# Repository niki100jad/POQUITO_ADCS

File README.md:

# POQUITO_ADCS

An ADCS PCB for a PocketQube, designed for the [QUBIK platform](https://libre.space/projects/qubik/).

This project is based on the https://gitlab.com/librespacefoundation/pq9ish/pq9ish-comms-vu-hw
project by the Libre Space Foundation, which was used for the [QUBIK](https://libre.space/projects/qubik/)
PocketQube missions.

## Features

- 3 magnetorquer drivers
- 1 9-axis Inertial Measurement Unit
- Based on an STM32L476 MCU
- Compatible with the [PQ9 standard](https://dataverse.nl/dataset.xhtml?persistentId=doi:10.34894/6MVBCZ)

## Images

## Related Projects

- [POQUITO Panels](https://github.com/kongr45gpen/POQUITO-panels)

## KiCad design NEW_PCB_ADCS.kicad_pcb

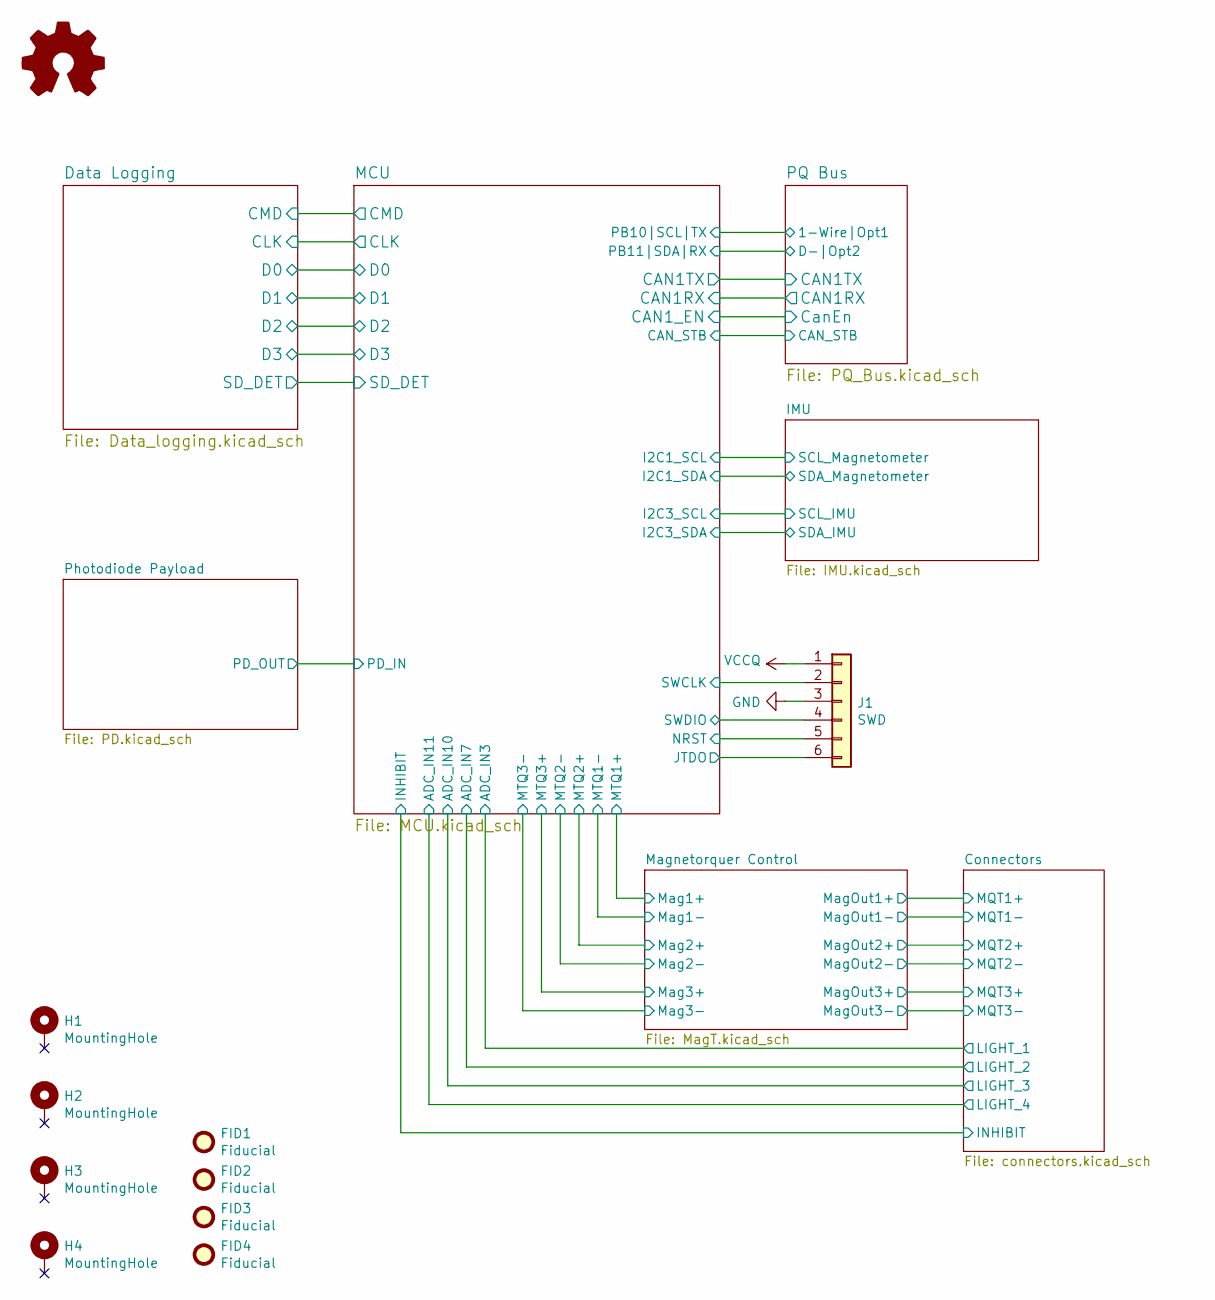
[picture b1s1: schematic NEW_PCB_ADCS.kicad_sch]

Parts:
FID1, FID2, FID3, FID4: Fiducial; Fiducial_0.5mm_Mask1.5mm
H1, H2, H3, H4: MountingHole; MountingHole_2.5mm_Pad
J1: SWD; Molex_PicoBlade_53261-0671_1x06-1MP_P1.25mm_Horizontal; Part Number 53261-0671

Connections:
/MCU/JTDO: J1.6; also elsewhere on the board
/MCU/NRST: J1.5; also elsewhere on the board
/MCU/SWCLK: J1.2; also elsewhere on the board
/MCU/SWDIO: J1.4; also elsewhere on the board
GND: J1.3; also elsewhere on the board
VCCQ: J1.1; also elsewhere on the board

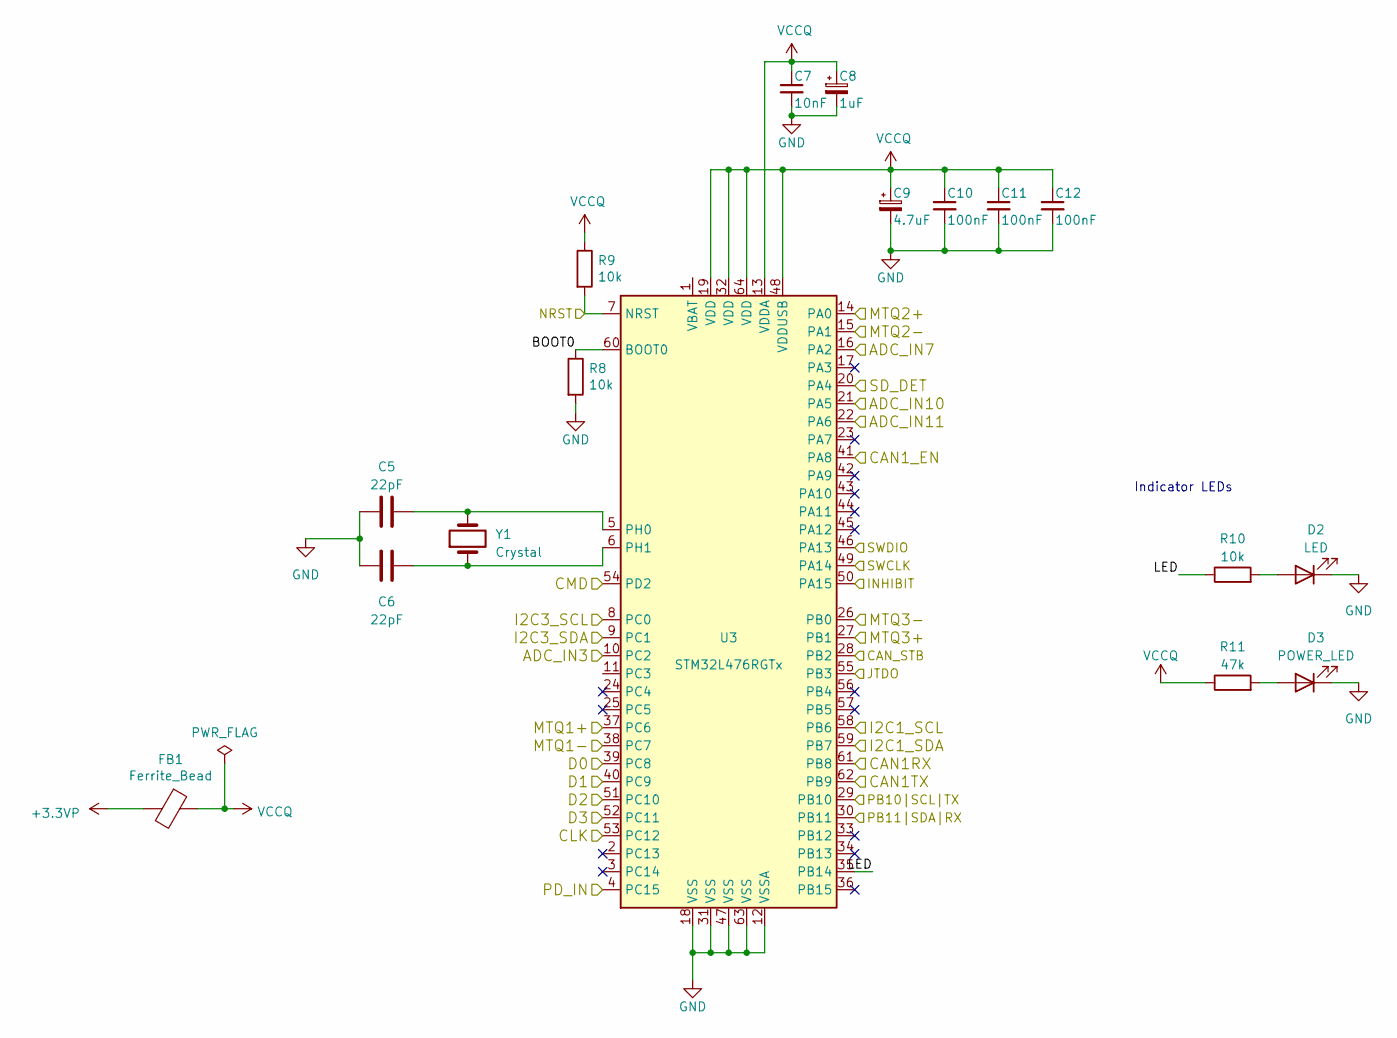
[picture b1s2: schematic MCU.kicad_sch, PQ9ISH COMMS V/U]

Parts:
C5, C6: 22pF; C_0603_1608Metric
C7: 10nF; C_0603_1608Metric_Pad1.08x0.95mm_HandSolder; Part Number C0603C103K9RACTU
C8: 1uF; C_0603_1608Metric_Pad1.08x0.95mm_HandSolder; Part Number CGB3B3X6S1A105K055AB
C9: 4.7uF; C_0603_1608Metric_Pad1.08x0.95mm_HandSolder; Part Number GRT188R60J475KE01D
C10, C11, C12: 100nF; C_0603_1608Metric; Part Number C0603C104K9RACTU
D2: LED; LED_0603_1608Metric; MPN LTST-C190KFKT
D3: POWER_LED; LED_0603_1608Metric; MPN LTST-C190KRKT
FB1: Ferrite_Bead; L_0603_1608Metric_Pad1.05x0.95mm_HandSolder; Part Number 742792664
R8, R9: 10k; R_0603_1608Metric; Part Number RE0603BRE0710KL
R10: 10k; R_0603_1608Metric; MPN RE0603BRE0710KL
R11: 47k; R_0603_1608Metric; Part Number RMCF0603FT47K0
U3: STM32L476RGTx; LQFP-64_10x10mm_P0.5mm; Part Number STM32L476RGT6
Y1: Crystal; Crystal_SMD_ECS_CSM3X-2Pin_7.6x4.1mm; MPN ECS-80-18-5PX-CKM-TR

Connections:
+3.3VP: FB1.2; also elsewhere on the board
/Connectors/INHIBIT: U3.50 (PA15); also elsewhere on the board
/Connectors/LIGHT_1: U3.10 (PC2); also elsewhere on the board
/Connectors/LIGHT_2: U3.16 (PA2); also elsewhere on the board
/Connectors/LIGHT_3: U3.21 (PA5); also elsewhere on the board
/Connectors/LIGHT_4: U3.22 (PA6); also elsewhere on the board
/Data Logging/CLK: U3.53 (PC12); also elsewhere on the board
/Data Logging/CMD: U3.54 (PD2); also elsewhere on the board
/Data Logging/D0: U3.39 (PC8); also elsewhere on the board
/Data Logging/D1: U3.40 (PC9); also elsewhere on the board
/Data Logging/D2: U3.51 (PC10); also elsewhere on the board
/Data Logging/D3: U3.52 (PC11); also elsewhere on the board
/Data Logging/SD_DET: U3.20 (PA4); also elsewhere on the board
/IMU/SCL_IMU: U3.8 (PC0); also elsewhere on the board
/IMU/SCL_Magnetometer: U3.58 (PB6); also elsewhere on the board
/IMU/SDA_IMU: U3.9 (PC1); also elsewhere on the board
/IMU/SDA_Magnetometer: U3.59 (PB7); also elsewhere on the board
/MCU/BOOT0: R8.1, U3.60 (BOOT0)
/MCU/CAN1RX: U3.61 (PB8); also elsewhere on the board
/MCU/CAN1TX: U3.62 (PB9); also elsewhere on the board
/MCU/CAN1_EN: U3.41 (PA8); also elsewhere on the board
/MCU/CAN_STB: U3.28 (PB2); also elsewhere on the board
/MCU/JTDO: U3.55 (PB3); also elsewhere on the board
/MCU/LED: R10.1, U3.35 (PB14)
/MCU/MTQ1+: U3.37 (PC6); also elsewhere on the board
/MCU/MTQ1-: U3.38 (PC7); also elsewhere on the board
/MCU/MTQ2+: U3.14 (PA0); also elsewhere on the board
/MCU/MTQ2-: U3.15 (PA1); also elsewhere on the board
/MCU/MTQ3+: U3.27 (PB1); also elsewhere on the board
/MCU/MTQ3-: U3.26 (PB0); also elsewhere on the board
/MCU/NRST: R9.2, U3.7 (NRST); also elsewhere on the board
/MCU/PB10|SCL|TX: U3.29 (PB10); also elsewhere on the board
/MCU/PB11|SDA|RX: U3.30 (PB11); also elsewhere on the board
/MCU/PD_IN: U3.4 (PC15); also elsewhere on the board
/MCU/SWCLK: U3.49 (PA14); also elsewhere on the board
/MCU/SWDIO: U3.46 (PA13); also elsewhere on the board
GND: C5.1, C6.1, C7.2, C8.2, C9.2, C10.2, C11.2, C12.2, D2.1 (K), D3.1 (K), R8.2, U3.12 (VSSA), U3.18 (VSS), U3.31 (VSS), U3.47 (VSS), U3.63 (VSS); also elsewhere on the board
unnamed: D2.2 (A), R10.2
unnamed: D3.2 (A), R11.2
unnamed: C5.2, U3.5 (PH0), Y1.2
unnamed: C6.2, U3.6 (PH1), Y1.1
VCCQ: C7.1, C8.1, C9.1, C10.1, C11.1, C12.1, FB1.1, R9.1, R11.1, U3.13 (VDDA), U3.19 (VDD), U3.32 (VDD), U3.48 (VDDUSB), U3.64 (VDD); also elsewhere on the board

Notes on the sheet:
Indicator LEDs

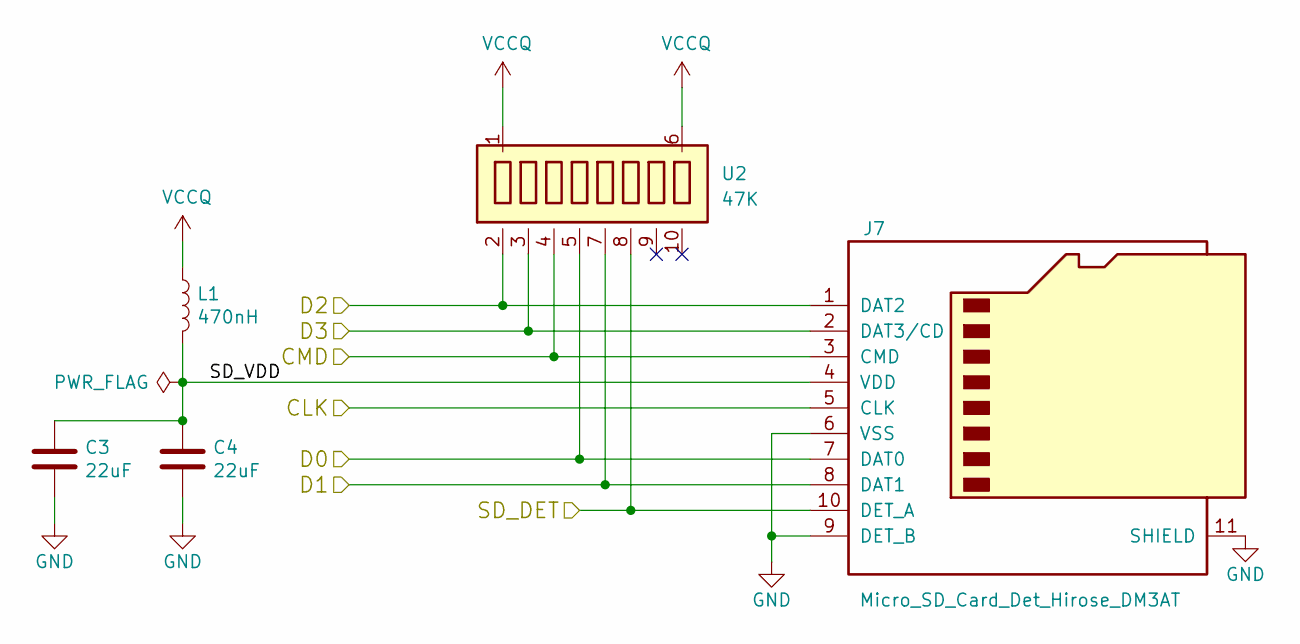
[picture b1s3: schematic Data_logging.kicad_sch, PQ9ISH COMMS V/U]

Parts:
C3, C4: 22uF; C_0603_1608Metric_Pad1.08x0.95mm_HandSolder; Part Number GRM188C80J226ME15D
J7: Micro_SD_Card_Det_Hirose_DM3AT; microSD_HC_Hirose_DM3D-SF; Part Number DM3D-SF
L1: 470nH; L_0603_1608Metric_Pad1.05x0.95mm_HandSolder; Part Number DFE18SANR47ME0L
U2: 47K; EXBD; Part Number EXBD10C473J

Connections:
/Data Logging/CLK: J7.5 (CLK); also elsewhere on the board
/Data Logging/CMD: J7.3 (CMD), U2.4 (R3); also elsewhere on the board
/Data Logging/D0: J7.7 (DAT0), U2.5 (R4); also elsewhere on the board
/Data Logging/D1: J7.8 (DAT1), U2.7 (R5); also elsewhere on the board
/Data Logging/D2: J7.1 (DAT2), U2.2 (R1); also elsewhere on the board
/Data Logging/D3: J7.2 (DAT3/CD), U2.3 (R2); also elsewhere on the board
/Data Logging/SD_DET: J7.10 (DET_A), U2.8 (R6); also elsewhere on the board
/Data Logging/SD_VDD: C3.1, C4.1, J7.4 (VDD), L1.2
GND: C3.2, C4.2, J7.6 (VSS), J7.9 (DET_B), J7.11 (SHIELD); also elsewhere on the board
VCCQ: L1.1, U2.1 (common), U2.6 (Common); also elsewhere on the board

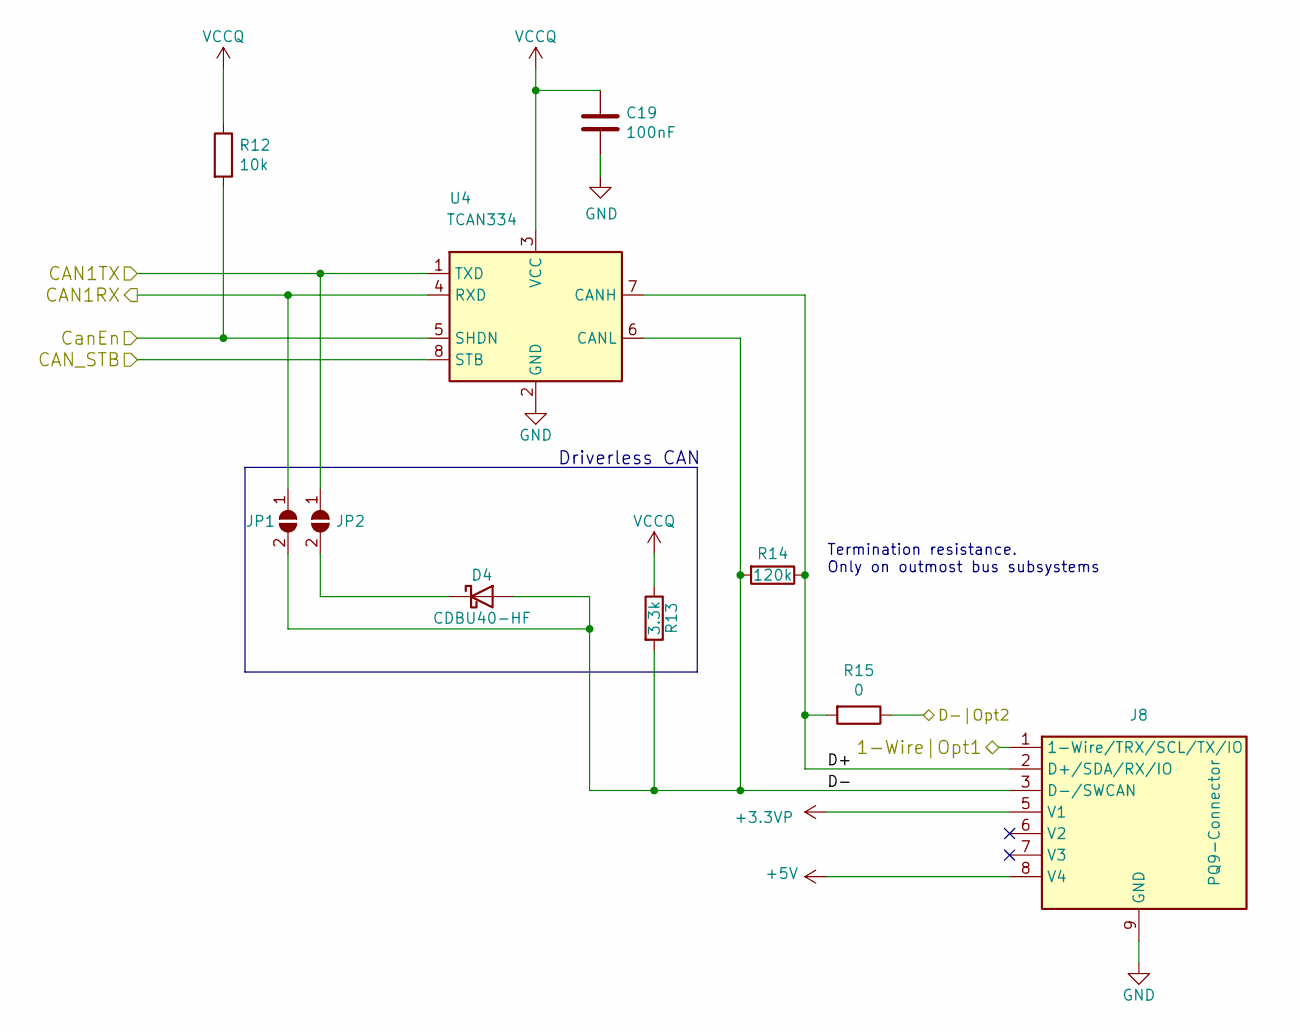
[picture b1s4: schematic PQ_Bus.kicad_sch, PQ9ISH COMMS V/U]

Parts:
C19: 100nF; C_0603_1608Metric; Part Number C0603C104K9RACTU
D4: CDBU40-HF; D_0603_1608Metric; Part Number CDBU40-HF
J8: PQ9-Connector; PinSocket_1x09_P2.00mm_Vertical; Part Number SQT-109-03-LS
JP1, JP2: SolderJumper_2_Open; SolderJumper-2_P1.3mm_Open_Pad1.0x1.5mm
R12: 10k; R_0603_1608Metric; Part Number RE0603BRE0710KL
R13: 3.3k; R_0603_1608Metric; Part Number MCT06030C3301FP500
R14: 120k; R_0603_1608Metric; Part Number CRCW0603120RFKEA
R15: 0; R_0603_1608Metric; Part Number RMCF0603ZT0R00
U4: TCAN334; SOT-23-8; Part Number TCAN334GDCNT

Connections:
+3.3VP: J8.5 (V1); also elsewhere on the board
+5V: J8.8 (V4)
/MCU/CAN1RX: JP1.1 (A), U4.4 (RXD); also elsewhere on the board
/MCU/CAN1TX: JP2.1 (A), U4.1 (TXD); also elsewhere on the board
/MCU/CAN1_EN: R12.2, U4.5 (SHDN); also elsewhere on the board
/MCU/CAN_STB: U4.8 (STB); also elsewhere on the board
/MCU/PB10|SCL|TX: J8.1 (1-Wire/TRX/SCL/TX/IO); also elsewhere on the board
/MCU/PB11|SDA|RX: R15.1; also elsewhere on the board
/PQ Bus/D+: J8.2 (D+/SDA/RX/IO), R14.1, R15.2, U4.7 (CANH)
/PQ Bus/D-: D4.2 (A), J8.3 (D-/SWCAN), JP1.2 (B), R13.2, R14.2, U4.6 (CANL)
GND: C19.2, J8.4 (GND), J8.9 (GND), U4.2 (GND); also elsewhere on the board
unnamed: D4.1 (K), JP2.2 (B)
VCCQ: C19.1, R12.1, R13.1, U4.3 (VCC); also elsewhere on the board

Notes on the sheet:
Driverless CAN
Termination resistance. Only on outmost bus subsystems

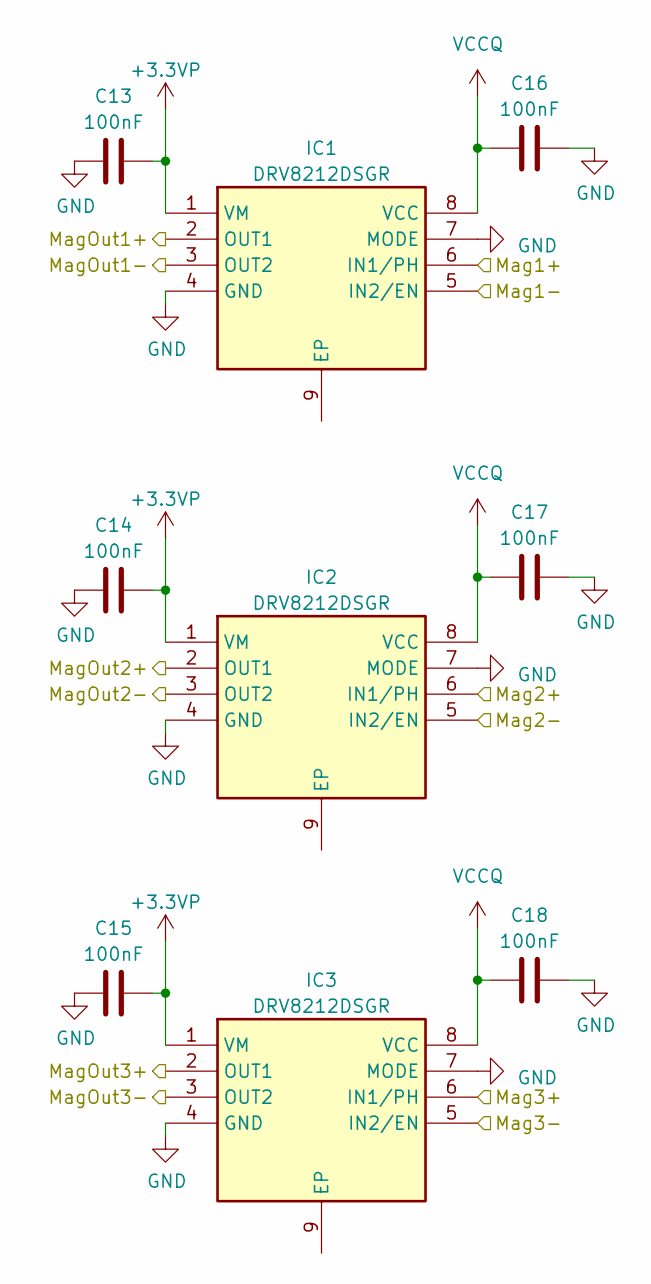
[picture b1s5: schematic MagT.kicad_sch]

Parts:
C13, C14, C15, C16, C17, C18: 100nF; C_0603_1608Metric; Part Number C0603C104K9RACTU
IC1, IC2, IC3: DRV8212DSGR; SON50P200X200X80-9N; Mouser Part Number 595-DRV8212DSGR

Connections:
+3.3VP: C13.2, C14.2, C15.2, IC1.1 (VM), IC2.1 (VM), IC3.1 (VM); also elsewhere on the board
/Connectors/MQT1+: IC1.2 (OUT1); also elsewhere on the board
/Connectors/MQT1-: IC1.3 (OUT2); also elsewhere on the board
/Connectors/MQT2+: IC2.2 (OUT1); also elsewhere on the board
/Connectors/MQT2-: IC2.3 (OUT2); also elsewhere on the board
/Connectors/MQT3+: IC3.2 (OUT1); also elsewhere on the board
/Connectors/MQT3-: IC3.3 (OUT2); also elsewhere on the board
/MCU/MTQ1+: IC1.6 (IN1/PH); also elsewhere on the board
/MCU/MTQ1-: IC1.5 (IN2/EN); also elsewhere on the board
/MCU/MTQ2+: IC2.6 (IN1/PH); also elsewhere on the board
/MCU/MTQ2-: IC2.5 (IN2/EN); also elsewhere on the board
/MCU/MTQ3+: IC3.6 (IN1/PH); also elsewhere on the board
/MCU/MTQ3-: IC3.5 (IN2/EN); also elsewhere on the board
GND: C13.1, C14.1, C15.1, C16.2, C17.2, C18.2, IC1.4 (GND), IC1.7 (MODE), IC1.9 (EP), IC2.4 (GND), IC2.7 (MODE), IC2.9 (EP), IC3.4 (GND), IC3.7 (MODE), IC3.9 (EP); also elsewhere on the board
VCCQ: C16.1, C17.1, C18.1, IC1.8 (VCC), IC2.8 (VCC), IC3.8 (VCC); also elsewhere on the board

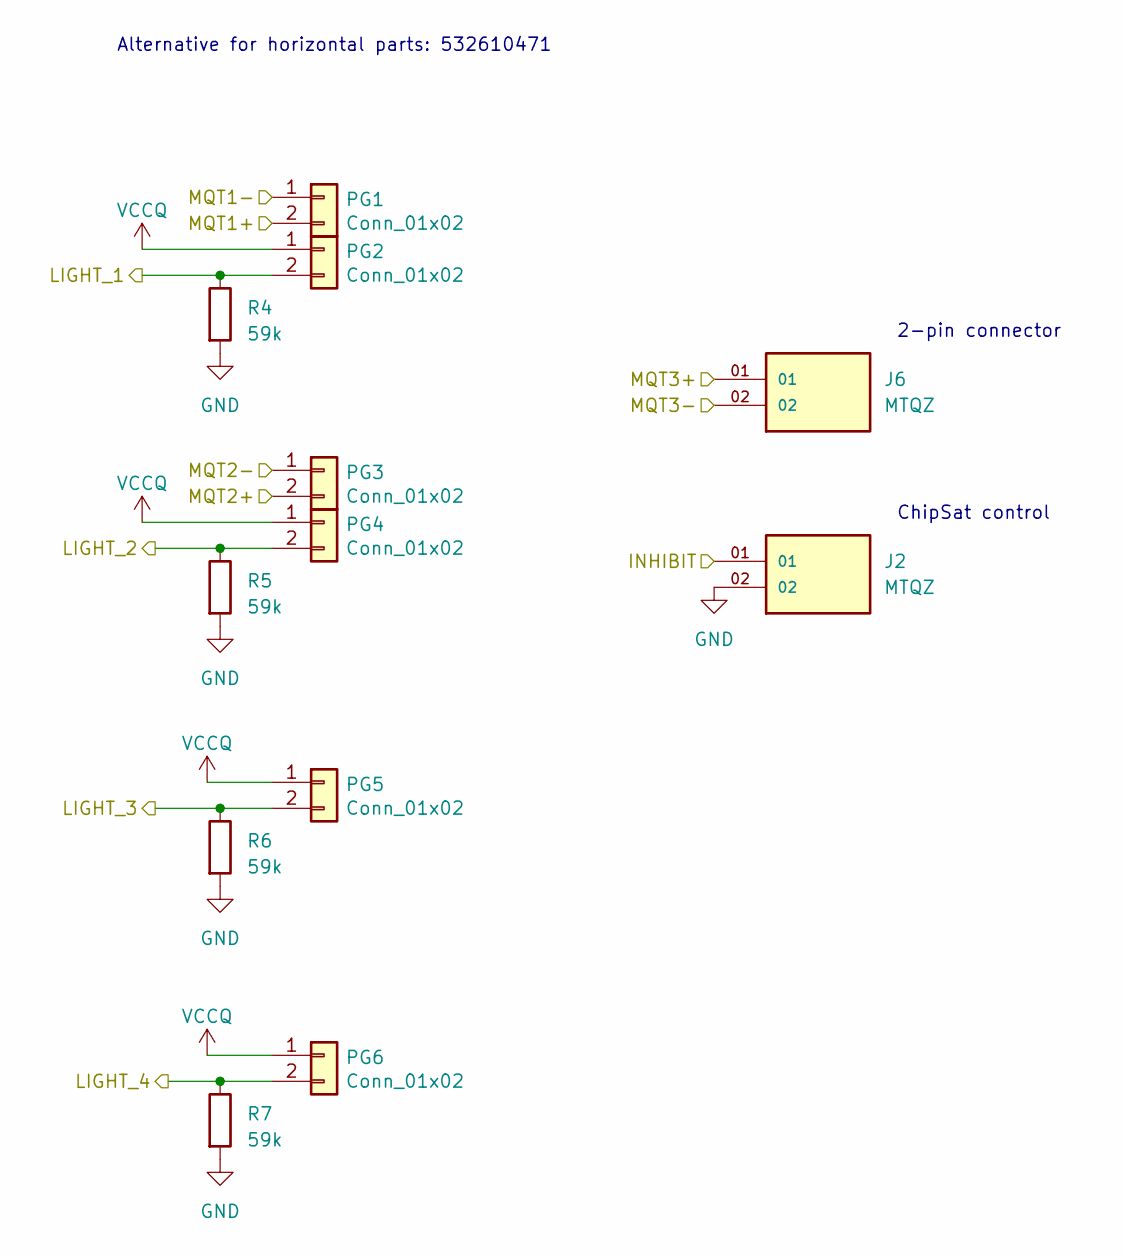
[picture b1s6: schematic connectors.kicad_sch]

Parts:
J2: MTQZ; JST_SH_SM02B-SRSS-TB_1x02-1MP_P1.00mm_Horizontal; Part Number SM02B-SRSS-TB
J6: MTQZ; SAMTEC_SQT-102-03-F-S; MPN SQT-102-03-F-S
PG1, PG2, PG3, PG4, PG5, PG6: Conn_01x02; MillMax_8290-22-002-20-001101_1x02_P2.54mm_Horizontal; Part Number 829-22-002-20-001101
R4, R5, R6, R7: 59k; LED_0805_2012Metric_Pad1.15x1.40mm_HandSolder; MPN ERA-6AEB5902V

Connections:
/Connectors/INHIBIT: J2.01; also elsewhere on the board
/Connectors/LIGHT_1: PG2.2, R4.1; also elsewhere on the board
/Connectors/LIGHT_2: PG4.2, R5.1; also elsewhere on the board
/Connectors/LIGHT_3: PG5.2, R6.1; also elsewhere on the board
/Connectors/LIGHT_4: PG6.2, R7.1; also elsewhere on the board
/Connectors/MQT1+: PG1.2; also elsewhere on the board
/Connectors/MQT1-: PG1.1; also elsewhere on the board
/Connectors/MQT2+: PG3.2; also elsewhere on the board
/Connectors/MQT2-: PG3.1; also elsewhere on the board
/Connectors/MQT3+: J6.01; also elsewhere on the board
/Connectors/MQT3-: J6.02; also elsewhere on the board
GND: J2.02, R4.2, R5.2, R6.2, R7.2; also elsewhere on the board
VCCQ: PG2.1, PG4.1, PG5.1, PG6.1; also elsewhere on the board

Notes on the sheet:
Alternative for horizontal parts: 532610471
ChipSat control
2-pin connector

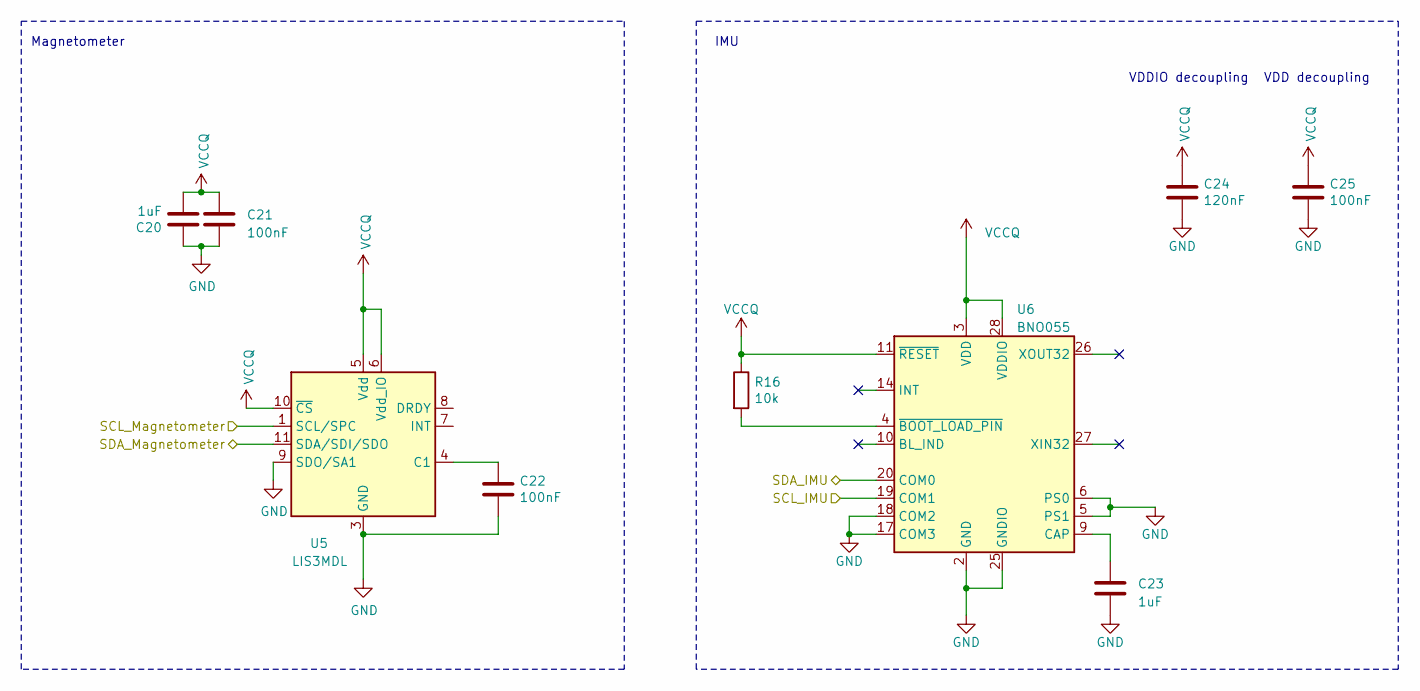
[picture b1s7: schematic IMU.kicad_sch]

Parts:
C20, C23: 1uF; C_0603_1608Metric; Part Number C0603C104K9RACTU
C21, C22, C25: 100nF; C_0603_1608Metric; Part Number C0603C104K9RACTU
C24: 120nF; C_0603_1608Metric; Part Number C0603C124J4RACTU
R16: 10k; R_0603_1608Metric; Part Number RE0603BRE0710KL
U5: LIS3MDL; LGA-12_2x2mm_P0.5mm; Part Number LIS3MDLTR
U6: BNO055; LGA-28_5.2x3.8mm_P0.5mm; Part Number BNO055

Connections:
/IMU/SCL_IMU: U6.19 (COM1); also elsewhere on the board
/IMU/SCL_Magnetometer: U5.1 (SCL/SPC); also elsewhere on the board
/IMU/SDA_IMU: U6.20 (COM0); also elsewhere on the board
/IMU/SDA_Magnetometer: U5.11 (SDA/SDI/SDO); also elsewhere on the board
GND: C20.1, C21.1, C22.2, C23.2, C24.2, C25.2, U5.2 (GND), U5.3 (GND), U5.9 (SDO/SA1), U5.12 (GND), U6.2 (GND), U6.5 (PS1), U6.6 (PS0), U6.15 (PIN15), U6.16 (PIN16), U6.17 (COM3), U6.18 (COM2), U6.25 (GNDIO); also elsewhere on the board
unnamed: C22.1, U5.4 (C1)
unnamed: C23.1, U6.9 (CAP)
unnamed: R16.2, U6.4 (~BOOT_LOAD_PIN)
VCCQ: C20.2, C21.2, C24.1, C25.1, R16.1, U5.5 (Vdd), U5.6 (Vdd_IO), U5.10 (~CS), U6.3 (VDD), U6.11 (~RESET), U6.28 (VDDIO); also elsewhere on the board

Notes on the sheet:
VDDIO decoupling
Magnetometer
IMU
VDD decoupling

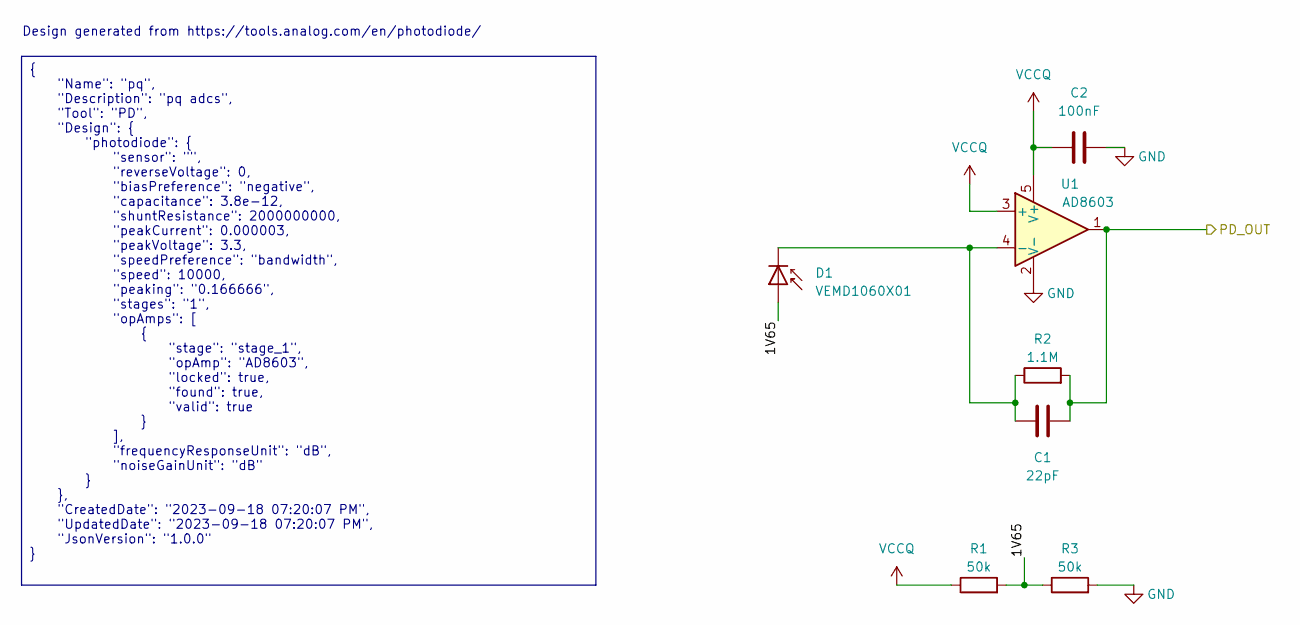
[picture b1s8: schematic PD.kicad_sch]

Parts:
C1: 22pF; C_0603_1608Metric
C2: 100nF; C_0603_1608Metric; Part Number C0603C104K9RACTU
D1: VEMD1060X01; LED_0805_2012Metric_Pad1.15x1.40mm_HandSolder; MPN VEMD1060X01
R1, R3: 50k; R_0603_1608Metric; Part Number RT0603BRD0750KL
R2: 1.1M; R_0603_1608Metric; Part Number AC0603FR-071M1L
U1: AD8603; TSOT-23-5; Part Number AD8603AUJZ-REEL

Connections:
/MCU/PD_IN: C1.1, R2.2, U1.1; also elsewhere on the board
/Photodiode Payload/1V65: D1.2 (A), R1.2, R3.1
GND: C2.2, R3.2, U1.2 (V-); also elsewhere on the board
unnamed: C1.2, D1.1 (K), R2.1, U1.4 (-)
VCCQ: C2.1, R1.1, U1.3 (+), U1.5 (V+); also elsewhere on the board

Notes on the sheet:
{ "Name": "pq", "Description": "pq adcs", "Tool": "PD", "Design": { "photodiode": { "sensor": "", "reverseVoltage": 0, "biasPreference": "negative", "capacitance": 3.8e-12, "shuntResistance": 2000000000, "peakCurrent": 0.000003, "peakVoltage": 3.3, "speedPreference": "bandwidth", "speed": 10000, "p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
Design generated from https://tools.analog.com/en/photodiode/

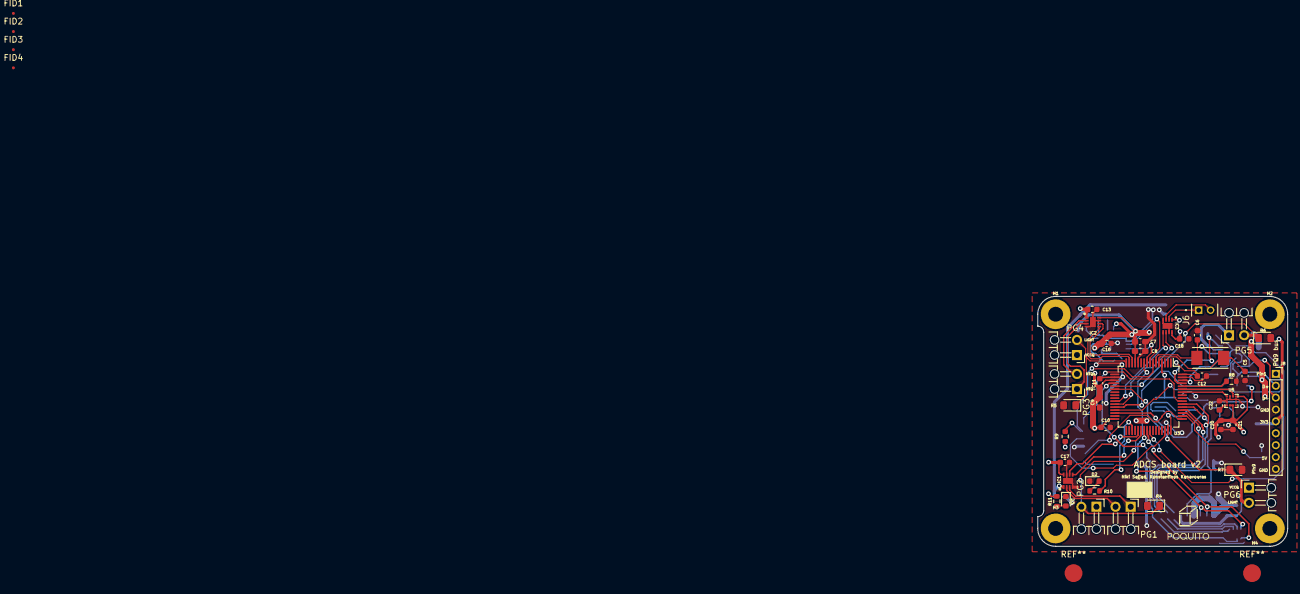
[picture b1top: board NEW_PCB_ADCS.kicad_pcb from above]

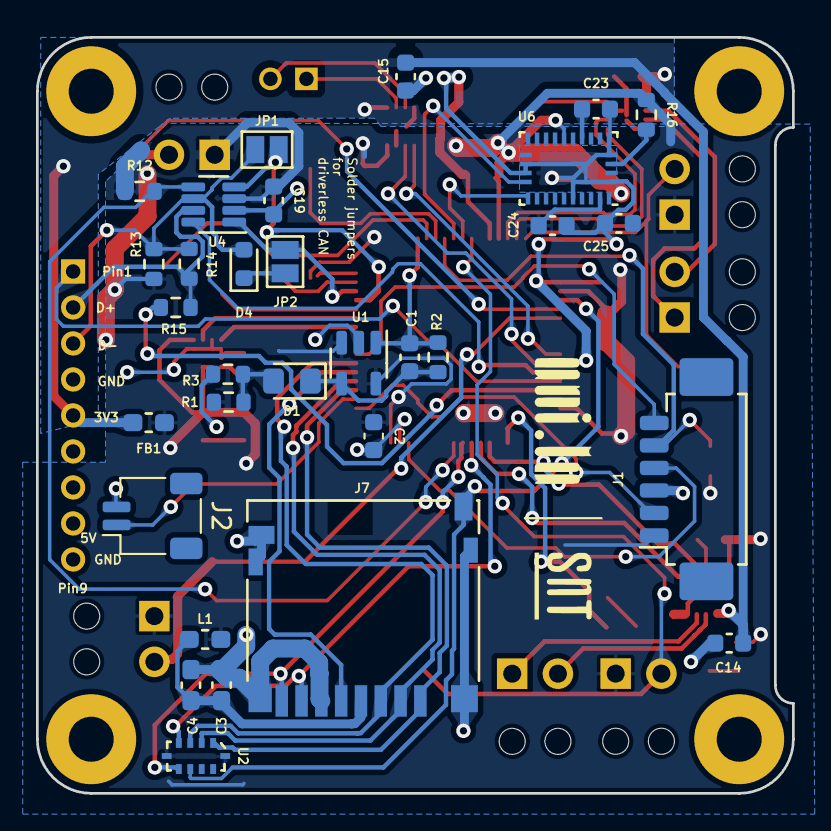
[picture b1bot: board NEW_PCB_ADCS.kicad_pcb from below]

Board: 2 copper layers, 42.0 x 42.0 mm, 78 parts (31 on the bottom side), 57 nets.

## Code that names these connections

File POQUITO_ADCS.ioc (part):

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Mcu.Name=STM32L476R(C-E-G)Tx
Mcu.Package=LQFP64
Mcu.UserName=STM32L476RGTx
PA0.Signal=S_TIM5_CH1
PA1.Signal=S_TIM5_CH2
PA13\ (JTMS-SWDIO).Mode=Trace_Asynchronous_SW
PA13\ (JTMS-SWDIO).Signal=SYS_JTMS-SWDIO
PA14\ (JTCK-SWCLK).Mode=Trace_Asynchronous_SW
PA14\ (JTCK-SWCLK).Signal=SYS_JTCK-SWCLK
PA4.Signal=GPIO_Input
PA6.Signal=S_TIM3_CH1
PA7.Signal=S_TIM3_CH2
PA8.GPIOParameters=PinState,GPIO_Label
PA8.GPIO_Label=CAN_DRV_EN
PA8.PinState=GPIO_PIN_SET
PA8.Signal=GPIO_Output
PB0.Signal=S_TIM3_CH3
PB1.Signal=S_TIM3_CH4
PB10.GPIOParameters=GPIO_Label
PB10.GPIO_Label=PQ_2
PB10.Signal=GPIO_Input
PB11.GPIOParameters=GPIO_Label
PB11.GPIO_Label=PQ_1
PB11.Signal=GPIO_Input
PB2.Signal=GPIO_Output
PB3\ (JTDO-TRACESWO).Mode=Trace_Asynchronous_SW
PB3\ (JTDO-TRACESWO).Signal=SYS_JTDO-SWO
PB6.GPIOParameters=GPIO_Label
PB6.GPIO_Label=I2C_IMU_SCL
PB6.Mode=I2C
PB6.Signal=I2C1_SCL
PB7.GPIOParameters=GPIO_Label
PB7.GPIO_Label=I2C_IMU_SDA
PB7.Mode=I2C
PB7.Signal=I2C1_SDA
PB8.GPIOParameters=GPIO_Speed,GPIO_Label,GPIO_Mode
PB8.GPIO_Label=CAN1_RX
PB8.GPIO_Mode=GPIO_MODE_AF_PP
PB8.GPIO_Speed=GPIO_SPEED_FREQ_VERY_HIGH
PB8.Mode=CAN_Activate
PB8.Signal=CAN1_RX
PB9.GPIOParameters=GPIO_Label
PB9.GPIO_Label=CAN1_TX
PB9.Mode=CAN_Activate
PB9.Signal=CAN1_TX
PC0.GPIOParameters=GPIO_Label
PC0.GPIO_Label=I2C_MAG_SCL
PC0.Mode=I2C
PC0.Signal=I2C3_SCL
PC1.GPIOParameters=GPIO_Label
PC1.GPIO_Label=I2C_MAG_SDA
PC1.Mode=I2C
PC1.Signal=I2C3_SDA
PC10.Mode=SD_4_bits_Wide_bus
PC10.Signal=SDMMC1_D2
PC11.Mode=SD_4_bits_Wide_bus
PC11.Signal=SDMMC1_D3
PC12.Mode=SD_4_bits_Wide_bus
PC12.Signal=SDMMC1_CK
PC13.GPIOParameters=GPIO_Label
PC13.GPIO_Label=CAN STB
PC13.Signal=GPIO_Output
PC4.Mode=IrDA
PC4.Signal=USART3_TX
PC5.GPIOParameters=GPIO_Label
PC5.GPIO_Label=IRDA_RX
PC5.Mode=IrDA
PC5.Signal=USART3_RX
PC8.Mode=SD_4_bits_Wide_bus
PC8.Signal=SDMMC1_D0
PC9.Mode=SD_4_bits_Wide_bus
PC9.Signal=SDMMC1_D1
PD2.Mode=SD_4_bits_Wide_bus
PD2.Signal=SDMMC1_CMD
PH0-OSC_IN\ (PH0).Mode=HSE-External-Oscillator
PH0-OSC_IN\ (PH0).Signal=RCC_OSC_IN
PH1-OSC_OUT\ (PH1).Mode=HSE-External-Oscillator
PH1-OSC_OUT\ (PH1).Signal=RCC_OSC_OUT
RCC.HSE_VALUE=16000000
RCC.SYSCLKFreq_VALUE=32000000
RCC.SYSCLKSource=RCC_SYSCLKSOURCE_PLLCLK
board=NUCLEO-L476RG
boardIOC=true

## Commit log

2023-09-05 Remove useless files and add some git boilerplates
2023-09-05 Actually add .git boilerplate files
2023-09-18 Add a license
    Closes #1
2023-09-18 Magnetometer fixes\n\nCloses #2
2023-09-18 IMU schematic fixes
    Closes #3
2023-09-18 Clean-up schematic
    Closes #4
2023-09-18 Add I2C multiplexer
2023-09-18 Add connections between existing sheets
2023-09-18 Add PD circuit
2023-09-18 Reannotate schematic
2023-10-13 Create PCB layout and routing
2023-10-17 Cleanup a few things
2023-10-26 most unconnected items are connected
2023-11-03 fix mistake
2023-11-03 Fix some issues
2023-11-03 Add silk screen
2023-11-07 Remove cache
2023-11-07 Remove paste from connectors, relink GND mounting pins
2023-11-07 Oops...forgot to save
2023-12-18 Add some more documentation and proper attribution
2023-12-19 Add missing old license content
2023-12-19 Use pogo pins; move diode to back
2023-12-22 Flip misaligned pogo pins
2023-12-22 Fix license source
2023-12-28 Update wrong MPNs
2023-12-28 Add ChipSat inhibit
2023-12-28 Add teardrops
2024-01-15 Update some part numbers
2024-01-24 Add fiducials
2024-01-30 Fix PTH mounting holes for MTQ
2024-01-30 Add cutout for panel L
2024-01-31 Fix outline DRC
2024-05-15 Update project to kicad 8
2024-05-20 Fix footprints, brought to you by Spyros

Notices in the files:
Data_logging.kicad_sch:
CERN OHLv1.2
